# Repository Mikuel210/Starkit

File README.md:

Starkit is a thrust vector controlled electric model rocket designed for propulsive landings

## Project description

I'm building an electric model rocket capable of taking off vertically, hovering and landing propulsively by using thrust vector control (TVC).

- **Propulsion**: I'm using two counter rotating brushless motors and 7" propellers. Each motor is powered by its own 6S LiPo battery and 60A ESC.
- **Avionics**: The main flight computer is an ESP32. I'm using an MPU9250 for orientation and a TF-Luna LiDAR for measuring altitude.
- **Control**: I'm using four TVC vanes driven by four Corona DS918MG servos.
- **Software**: I'm using PID algorithms for controlling orientation and altitude.
- **Structure**: The structure is built from 5mm carbon fiber rods. The rods are locked into 3D printed structural parts that hold mounts to attach the components as well.
- **Landing gear**: I'm using deployable landing gear, actuated by four SG90 servos. Each landing leg is made of a two part design that locks the leg in place once deployed.

## Goal of the project

**To learn and have fun by building an electric model rocket capable of lifting off, hovering and landing propulsively**

I want to build a fully reusable vehicle capable of landing propulsively through thrust vector control. If the rocket is capable of performing a 1 meter hop and hover for 30 seconds, I will consider it a success.

### Why I'm building this project

- To learn about avionics and PCB design
- To learn about software, communication and control systems
- To learn about rocket design
- To learn about CAD and project planning

## PCB

## Wiring diagram

## BOM

| Item                      | Amount | Amount owned | Amount needed | Unit price (€) | Total price (€)    | Link                                                                                                                                                                                                                                                                                                                                                                                                                                                                                                                                                                                                                                                                                                                                                 | Configuration           |
| ------------------------- | ------ | ------------ | ------------- | -------------- | ------------------ | ---------------------------------------------------------------------------------------------------------------------------------------------------------------------------------------------------------------------------------------------------------------------------------------------------------------------------------------------------------------------------------------------------------------------------------------------------------------------------------------------------------------------------------------------------------------------------------------------------------------------------------------------------------------------------------------------------------------------------------------------------- | ----------------------- |
| Batteries                 | 2      |              | 2             | 21,50 €        | 42,99 €            | https://www.amazon.es/HRB-reemplazo-bater%C3%ADa-helic%C3%B3pteros-multicopter/dp/B08TBQKL5B?__mk_es_ES=%C3%85M%C3%85%C5%BD%C3%95%C3%91&crid=2U28Y8KBC8R6M&dib=eyJ2IjoiMSJ9.LXgd79wYVsAlYN8cnheOxOF4z8WHjVPr62UBUdfznEQJUaDWFurwLly_Y13YaV3RCzLjk-IxK2Fx9W1uenqtNgzYBgRNuDVj7gfl4NINt41JqlagWhER4W6rHc6h9dRlsdaZ5Ce64atc4zXVoRv13AauXNFDNE45YwVqKeBIqNpf9GEJRRZUNdxUH4Pl90CMlF84Z880-oE7fsl0TjBh_6v0BYAjIXQ1fz_dwNbMJv1PuqQj3wlPIk55cYDsAPc5loPb8o5-Sp9KXF6ivD4jsehSx9MazX_DaFdfXWazJdw.h3kvJfKKLavn0LHZoaGCOh_W49E9_VzB4I3oYA7u7xY&dib_tag=se&keywords=6s+lipo&qid=1749288373&sprefix=6s+lip%2Caps%2C153&sr=8-46                                                                                                                                    |                         |
| ESCs                      | 2      |              | 2             | 18,59 €        | 37,18 €            | https://es.aliexpress.com/item/1005007477046035.html?spm=a2g0o.productlist.main.3.386577c09KkIA9&algo_pvid=33246dc7-7638-46ad-b82a-8027f90a3399&algo_exp_id=33246dc7-7638-46ad-b82a-8027f90a3399-2&pdp_ext_f=%7B%22order%22%3A%221041%22%2C%22eval%22%3A%221%22%2C%22orig_sl_item_id%22%3A%221005007477046035%22%2C%22orig_item_id%22%3A%221005006909796101%22%7D&pdp_npi=4%40dis%21EUR%2125.40%2112.19%21%21%21203.69%2197.76%21%40211b80e117493716014395182e0aa8%2112000040910350509%21sea%21ES%210%21ABX&curPageLogUid=Syvg8hf9kOqB&utparam-url=scene%3Asearch%7Cquery_from%3A#nav-specification                                                                                                                                                  | Flier 60A V2            |
| Motors                    | 2      |              | 2             | 19,59 €        | 39,18 €            | https://es.aliexpress.com/item/1005005975992937.html?spm=a2g0o.productlist.main.8.504bn3sun3supR&algo_pvid=37cce2c5-c8eb-4d84-a651-7cc254a33470&algo_exp_id=37cce2c5-c8eb-4d84-a651-7cc254a33470-7&pdp_ext_f=%7B%22order%22%3A%227%22%2C%22eval%22%3A%221%22%7D&pdp_npi=4%40dis%21EUR%2122.93%2119.49%21%21%2125.86%2121.98%21%40211b816617499737898785401ed436%2112000035134152652%21sea%21ES%210%21ABX&curPageLogUid=8ZItec0QIfi4&utparam-url=scene%3Asearch%7Cquery_from%3A                                                                                                                                                                                                                                                                       | 1PCS KV1300             |
| Propellers                | 2      |              | 2             | 2,50 €         | 5,00 €             | https://immersion974.com/products/2-paires-dalprop-racerstar-cyclone-t7056c-7056-7x5-6x3-longue-portee-fpv-courses-helice?variant=37636740907168                                                                                                                                                                                                                                                                                                                                                                                                                                                                                                                                                                                                     |                         |
| Leg servos                | 4      | 2            | 2             | 1,07 €         | 2,13 €             | https://es.aliexpress.com/item/1005006572297006.html?spm=a2g0o.productlist.main.2.6d327beakrE4nq&algo_pvid=2c0991c4-8ac1-4d60-aff7-97e9de4a23dd&algo_exp_id=2c0991c4-8ac1-4d60-aff7-97e9de4a23dd-1&pdp_ext_f=%7B%22order%22%3A%224689%22%2C%22eval%22%3A%221%22%7D&pdp_npi=4%40dis%21EUR%212.71%212.21%21%21%213.03%212.47%21%402103919917492886741265488ec7a9%2112000037705759120%21sea%21ES%210%21ABX&curPageLogUid=Mx4vlddFCr1O&utparam-url=scene%3Asearch%7Cquery_from%3A                                                                                                                                                                                                                                                                        | 2Pcs 180 Degree         |
| TVC servos                | 4      |              | 4             | 9,64 €         | 38,55 €            | https://es.aliexpress.com/item/1005002272302617.html                                                                                                                                                                                                                                                                                                                                                                                                                                                                                                                                                                                                                                                                                                 | With 25mm arm x4        |
| Structure rods            | 20     |              | 20            | 2,03 €         | 40,50 €            | https://es.aliexpress.com/item/1005004263451845.html?spm=a2g0o.productlist.main.1.761ceYmheYmhd6&algo_pvid=e5415fe3-4327-4676-a66d-658a9bb2db3f&algo_exp_id=e5415fe3-4327-4676-a66d-658a9bb2db3f-0&pdp_ext_f=%7B%22order%22%3A%221623%22%2C%22eval%22%3A%221%22%7D&pdp_npi=4%40dis%21EUR%213.57%213.07%21%21%2128.65%2124.64%21%40211b431017492896503426651e8be3%2112000038328676176%21sea%21ES%210%21ABX&curPageLogUid=qhARfsXnKG4c&utparam-url=scene%3Asearch%7Cquery_from%3A                                                                                                                                                                                                                                                                      | 5Pcs 5.0x500mm          |
| Leg struts                | 8      |              | 8             | 0,77 €         | 6,19 €             | https://es.aliexpress.com/item/1005004263451845.html?spm=a2g0o.productlist.main.1.761ceYmheYmhd6&algo_pvid=e5415fe3-4327-4676-a66d-658a9bb2db3f&algo_exp_id=e5415fe3-4327-4676-a66d-658a9bb2db3f-0&pdp_ext_f=%7B%22order%22%3A%221623%22%2C%22eval%22%3A%221%22%7D&pdp_npi=4%40dis%21EUR%213.57%213.07%21%21%2128.65%2124.64%21%40211b431017492896503426651e8be3%2112000038328676176%21sea%21ES%210%21ABX&curPageLogUid=qhARfsXnKG4c&utparam-url=scene%3Asearch%7Cquery_from%3A                                                                                                                                                                                                                                                                      | 10Pcs 3.0x500mm         |
| Leg springs               | 4      |              | 4             | 0,43 €         | 1,73 €             | https://es.aliexpress.com/item/4000250320601.html?spm=a2g0o.productlist.main.1.5f69144ec1rYDm&algo_pvid=0e2fdce4-f2c5-40f6-83f7-67ac9305241b&algo_exp_id=0e2fdce4-f2c5-40f6-83f7-67ac9305241b-0&pdp_ext_f=%7B%22order%22%3A%221365%22%2C%22eval%22%3A%221%22%7D&pdp_npi=4%40dis%21EUR%211.34%210.99%21%21%211.50%211.11%21%40211b617b17492888951613089eab25%2112000026870638881%21sea%21ES%210%21ABX&curPageLogUid=aOtvWOKUPPKC&utparam-url=scene%3Asearch%7Cquery_from%3A                                                                                                                                                                                                                                                                           | 30mm 0.3 x 4            |
| PETG filament             | 1      | 1            | 0             | 16,99 €        | 0,00 €             | https://eu.store.bambulab.com/es/products/petg-translucent?id=49192018149724                                                                                                                                                                                                                                                                                                                                                                                                                                                                                                                                                                                                                                                                         |                         |
| Velcro                    | 10     |              | 10            | 0,15 €         | 1,53 €             | https://es.aliexpress.com/item/1005008063390791.html?spm=a2g0o.productlist.main.7.7935CBDhCBDhJD&algo_pvid=82ab8097-120f-49c0-bfd2-9221ed149b58&algo_exp_id=82ab8097-120f-49c0-bfd2-9221ed149b58-6&pdp_ext_f=%7B%22order%22%3A%222119%22%2C%22eval%22%3A%221%22%7D&pdp_npi=4%40dis%21EUR%211.15%210.99%21%21%219.21%217.95%21%4021039a5b17492912680996755eeb12%2112000043504951494%21sea%21ES%210%21ABX&curPageLogUid=XN77MbkCJ60X&utparam-url=scene%3Asearch%7Cquery_from%3A                                                                                                                                                                                                                                                                        | Rectangle 16x70mm 10pcs |
| Bullet connectors         | 6      |              | 6             | 0,28 €         | 1,66 €             | https://es.aliexpress.com/item/1005006400659486.html?spm=a2g0o.productlist.main.1.37683ccbXgkhPr&algo_pvid=22aa2fc1-add9-4555-bb5d-8170122417b8&algo_exp_id=22aa2fc1-add9-4555-bb5d-8170122417b8-0&pdp_ext_f=%7B%22order%22%3A%223980%22%2C%22eval%22%3A%221%22%7D&pdp_npi=4%40dis%21EUR%211.31%210.99%21%21%211.46%211.10%21%402103867617492898094714028e0921%2112000037032813999%21sea%21ES%210%21ABX&curPageLogUid=pehdywiyloSB&utparam-url=scene%3Asearch%7Cquery_from%3A                                                                                                                                                                                                                                                                        | 6Pair 4.0mm             |
| Cable for motor extension | 1      |              | 1             | 5,59 €         | 5,59 €             | https://es.aliexpress.com/item/1005006566120439.html?spm=a2g0o.productlist.main.1.57f039b470LHsH&algo_pvid=eb01c303-fb0d-48fe-b015-28dc3583114b&algo_exp_id=eb01c303-fb0d-48fe-b015-28dc3583114b-0&pdp_ext_f=%7B%22order%22%3A%224259%22%2C%22eval%22%3A%221%22%7D&pdp_npi=4%40dis%21EUR%216.56%215.40%21%21%2152.57%2143.28%21%40211b816617492903787692996e86a8%2112000037691464138%21sea%21ES%210%21ABX&curPageLogUid=ippPKrVhFn3g&utparam-url=scene%3Asearch%7Cquery_from%3A                                                                                                                                                                                                                                                                      | 3m 12 AWG               |
| Heat shrunk tubing        | 1      |              | 1             | 4,46 €         | 4,46 €             | https://es.aliexpress.com/item/1005005188307524.html?spm=a2g0o.tesla.0.0.4dcej0Zsj0ZsUd&pdp_npi=4%40dis%21EUR%212%2C10€%210%2C99€%21%21%21%21%21%40211b612817500001384372689ec846%2112000032032038883%21btf%21%21%21&afTraceInfo=1005005188307524__pc__c_ppc_item_bridge_pc_main__IQwes0f__1750000138532&gatewayAdapt=glo2esp                                                                                                                                                                                                                                                                                                                                                                                                                        | 580pcs in box           |
| Cable for components      | 1      |              | 1             | 2,44 €         | 2,44 €             | https://es.aliexpress.com/item/1005006566120439.html?spm=a2g0o.productlist.main.2.11a87387Kycknd&algo_pvid=198a24ce-2649-422a-be70-759f7e4ad08c&algo_exp_id=198a24ce-2649-422a-be70-759f7e4ad08c-1&pdp_ext_f=%7B%22order%22%3A%224277%22%2C%22eval%22%3A%221%22%7D&pdp_npi=4%40dis%21EUR%216.49%215.34%21%21%2152.57%2143.24%21%40210384cc17501889223512784eabb6%2112000037691464138%21sea%21ES%210%21ABX&curPageLogUid=Az62DYRaIplh&utparam-url=scene%3Asearch%7Cquery_from%3A                                                                                                                                                                                                                                                                      | Black 5M 20AWG          |
| Charger                   | 1      |              | 1             | 19,67 €        | 19,67 €            | https://es.aliexpress.com/item/1005007326920235.html?spm=a2g0o.productlist.main.25.1ee4130b71LMaE&utparam-url=scene%3Asearch%7Cquery_from%3Apc_back_same_best&algo_pvid=96a50608-e680-4398-9ac8-59a08becccd5&algo_exp_id=96a50608-e680-4398-9ac8-59a08becccd5&pdp_ext_f=%7B%22order%22%3A%224048%22%7D&pdp_npi=4%40dis%21EUR%2156.71%2117.36%21%21%21454.74%21139.15%21%40211b628117492908826713158e85fb%2112000040281503044%21sea%21ES%210%21ABX                                                                                                                                                                                                                                                                                                    |                         |
| LiPo bag                  | 2      |              | 2             | 5,56 €         | 11,12 €            | https://www.amazon.es/KUBDPQOR-bater%C3%ADa-Ign%C3%ADfuga-Explosiones-Proteger/dp/B0D6WDVMMQ?dib=eyJ2IjoiMSJ9.EBP3VYs7h0d46i2jEdIxCKP0RCziNsbeAdRnjLeE8Segq2aCxgiG8TaUSG9pjhEP5kb4TCmJDvvTbySqxWheuOfQSJpC3GV0VFwi3erFFE_vtUzrdDW6SQzrTM4v1oX_-QL77Y4_ZPMVrz8BhAXiTVmv6VJYg3sTffhQAcX2qMmE-DzR8BOlpTaodYAHj2pwl0eXWOGXwQWWrb9GUDiV4g_7BaYk1vnk4mZcEWNol4aLK8bs5B2g2urb97TYCW6RdLv3nLkAx9yHx4zj7G-5H0YhJ4oDjEtXmhuVA_VQWWs.4HBTMUuzYBEyHpB2geBzHTSd5y7LK7zdPYDjDSmmhfM&dib_tag=se&keywords=lipo+safe&qid=1749291023&sr=8-12                                                                                                                                                                                                                           |                         |
| PCB                       | 1      |              | 1             | 0,00 €         | 0,00 €             | https://jlcpcb.com/es/                                                                                                                                                                                                                                                                                                                                                                                                                                                                                                                                                                                                                                                                                                                               |                         |
| LiDAR                     | 1      |              | 1             | 16,93 €        | 16,93 €            | https://es.aliexpress.com/item/1005007773724655.html?spm=a2g0o.detail.pcDetailTopMoreOtherSeller.1.d03cnvSMnvSM4O&gps-id=pcDetailTopMoreOtherSeller&scm=1007.40196.439370.0&scm_id=1007.40196.439370.0&scm-url=1007.40196.439370.0&pvid=257a845b-bd4b-41b9-8eb4-32116a834614&_t=gps-id:pcDetailTopMoreOtherSeller,scm-url:1007.40196.439370.0,pvid:257a845b-bd4b-41b9-8eb4-32116a834614,tpp_buckets:668%232846%238112%231997&pdp_ext_f=%7B%22order%22%3A%22236%22%2C%22eval%22%3A%221%22%2C%22sceneId%22%3A%2230050%22%7D&pdp_npi=4%40dis%21EUR%2157.01%2116.91%21%21%21460.14%21136.51%21%40211b680e17505431540684235eaa38%2112000042158078686%21rec%21ES%21%21ABX&utparam-url=scene%3ApcDetailTopMoreOtherSeller%7Cquery_from%3A#nav-specification |                         |
| IMU                       | 1      |              | 1             | 12,29 €        | 12,29 €            | https://www.amazon.es/MPU%E2%80%919250-giroscopio-magn%C3%A9tico-aceleraci%C3%B3n-medici%C3%B3n/dp/B0BJ31W6KR                                                                                                                                                                                                                                                                                                                                                                                                                                                                                                                                                                                                                                        |                         |
| ESP32                     | 1      |              | 1             | 4,99 €         | 4,99 €             | https://es.aliexpress.com/item/1005008256121637.html?spm=a2g0o.productlist.main.1.46f27592KkhDQ6&aem_p4p_detail=202506080321268011175419467780003631533&algo_pvid=4f7e4e87-e7b9-43e2-9669-503fdb80d1ae&algo_exp_id=4f7e4e87-e7b9-43e2-9669-503fdb80d1ae-0&pdp_ext_f=%7B%22order%22%3A%22257%22%2C%22eval%22%3A%221%22%7D&pdp_npi=4%40dis%21EUR%215.46%214.96%21%21%216.10%215.54%21%40211b6c1917493780866902562efb03%2112000044390358746%21sea%21ES%210%21ABX&curPageLogUid=CkoJWcgnXXZE&utparam-url=scene%3Asearch%7Cquery_from%3A&search_p4p_id=202506080321268011175419467780003631533_1#nav-review                                                                                                                                               | 32D-Type-C-1PCS         |
| Buzzer                    | 1      | 1            | 0             | 0,75 €         | 0,00 €             | https://es.aliexpress.com/item/1005007592230799.html?spm=a2g0o.productlist.main.1.356aC484C484k3&algo_pvid=819561e8-b375-4570-83e4-714f464b8131&algo_exp_id=819561e8-b375-4570-83e4-714f464b8131-0&pdp_ext_f=%7B%22order%22%3A%2246%22%2C%22eval%22%3A%221%22%7D&pdp_npi=4%40dis%21EUR%212.33%210.75%21%21%2118.73%215.99%21%40210390c217503419577143060ed746%2112000041421776769%21sea%21ES%210%21ABX&curPageLogUid=WB7zU00jnQbC&utparam-url=scene%3Asearch%7Cquery_from%3A                                                                                                                                                                                                                                                                         |                         |
| LED                       | 1      | 1            | 0             | 0,70 €         | 0,00 €             | https://es.aliexpress.com/item/1005006942561228.html?spm=a2g0o.productlist.main.2.4f4620eaffVXXM&algo_pvid=2d0dae61-9e8a-4390-b421-1c9e1a1cae35&algo_exp_id=2d0dae61-9e8a-4390-b421-1c9e1a1cae35-1&pdp_ext_f=%7B%22order%22%3A%2251%22%2C%22eval%22%3A%221%22%7D&pdp_npi=4%40dis%21EUR%212.68%210.70%21%21%2121.56%215.61%21%40211b80d117503420023265406e6673%2112000038806749170%21sea%21ES%210%21ABX&curPageLogUid=Ud7lEb62zfWF&utparam-url=scene%3Asearch%7Cquery_from%3A                                                                                                                                                                                                                                                                         |                         |
| Resistors                 | 4      | 4            | 0             | 0,19 €         | 0,00 €             | https://es.aliexpress.com/item/1005007345052730.html?spm=a2g0o.productlist.main.2.4daf4384BgtyYb&algo_pvid=6cfb8a2a-37b7-4e76-8c01-f36b3aa0684e&algo_exp_id=6cfb8a2a-37b7-4e76-8c01-f36b3aa0684e-1&pdp_ext_f=%7B%22order%22%3A%224627%22%2C%22eval%22%3A%221%22%2C%22orig_sl_item_id%22%3A%221005007345052730%22%2C%22orig_item_id%22%3A%221005007010335100%22%7D&pdp_npi=4%40dis%21EUR%211.60%210.77%21%21%2112.85%216.17%21%40211b807017503420350251565ec044%2112000040354424593%21sea%21ES%210%21ABX&curPageLogUid=8nPfyjNQNS36&utparam-url=scene%3Asearch%7Cquery_from%3A                                                                                                                                                                        |                         |
| Headers                   | 1      |              | 1             | 2,02 €         | 2,02 €             | https://es.aliexpress.com/item/4000873858801.html?spm=a2g0o.productlist.main.1.438aMcaxMcaxHA&algo_pvid=8948f835-3dba-4bb3-a6ef-0351d63cb6cf&algo_exp_id=8948f835-3dba-4bb3-a6ef-0351d63cb6cf-0&pdp_ext_f=%7B%22order%22%3A%223640%22%2C%22eval%22%3A%221%22%7D&pdp_npi=4%40dis%21EUR%212.03%211.53%21%21%212.27%211.71%21%40211b813b17503404308943254e449c%2110000010058190554%21sea%21ES%210%21ABX&curPageLogUid=zYO2SICB1heb&utparam-url=scene%3Asearch%7Cquery_from%3A#nav-specification                                                                                                                                                                                                                                                         |                         |
| Angled headers            | 1      |              | 1             | 1,24 €         | 1,24 €             | https://es.aliexpress.com/item/1005008210852764.html?spm=a2g0o.detail.pcDetailTopMoreOtherSeller.5.1eaeV432V432MN&gps-id=pcDetailTopMoreOtherSeller&scm=1007.40196.439370.0&scm_id=1007.40196.439370.0&scm-url=1007.40196.439370.0&pvid=2362691a-9cfa-40b6-b383-5963bc6e059a&_t=gps-id:pcDetailTopMoreOtherSeller,scm-url:1007.40196.439370.0,pvid:2362691a-9cfa-40b6-b383-5963bc6e059a,tpp_buckets:668%232846%238110%231995&pdp_ext_f=%7B%22order%22%3A%22162%22%2C%22eval%22%3A%221%22%2C%22sceneId%22%3A%2230050%22%7D&pdp_npi=4%40dis%21EUR%211.24%210.99%21%21%211.39%211.11%21%4021038df617505419994764643e6b41%2112000044248658299%21rec%21ES%21%21ABX&utparam-url=scene%3ApcDetailTopMoreOtherSeller%7Cquery_from%3A                         | 5Pin 5PCS               |
| Screw terminals           | 4      |              | 4             | 0,37 €         | 1,48 €             | https://es.aliexpress.com/item/1005003556955422.html?spm=a2g0o.productlist.main.3.3caf577cKYWN3O&algo_pvid=340ecbec-d2a6-419c-bd93-93956aa32efc&algo_exp_id=340ecbec-d2a6-419c-bd93-93956aa32efc-1&pdp_ext_f=%7B%22order%22%3A%22552%22%2C%22eval%22%3A%221%22%7D&pdp_npi=4%40dis%21EUR%211.59%210.99%21%21%211.78%211.11%21%40210390c217503411498531989ed743%2112000026274837536%21sea%21ES%210%21ABX&curPageLogUid=msIM3PVHPRlV&utparam-url=scene%3Asearch%7Cquery_from%3A                                                                                                                                                                                                                                                                         | 2Pin 5Pcs               |
| Magnetic balancer         | 1      |              | 1             | 10,52 €        | 10,52 €            | https://www.amazon.es/Hobbypower-Multirotor-Propeller-Magn%C3%A9tico-Quadcopter/dp/B00GSKSFM6?__mk_es_ES=%C3%85M%C3%85%C5%BD%C3%95%C3%91&crid=1Y3D0M00HPAML&dib=eyJ2IjoiMSJ9.TuTH0MKorCpoiaKcuztv5uWmJWleMAYXeDQycNbQ4IHivDQ105jsGrrjYZ11Sx7rg6FHVSvKujnNcWT_9lNPbTIiUqPn2WHdsZ_zTbJQcPzBM1D9I71DuqtkUYKXEyrq6ng_BWkLqkpwmIwsPoCh9qeQeEqdkKkKAp9_YUOeBDmXgSaBJmB1Kgr4bQ4joYWMVLeG3Xx2xtgtuxQfYcW465nYuV7QSnTvXNQ15mXIQQFIjNy7ab1Ct7_8X6uE0uhkFchynzrup0nNjkwCBmpCAtYj_57xiFfdTUPbxArW8O8.HO9O6JUpm8p1K876pSry3QmQJbRnl_hQBwxro1-oBcA&dib_tag=se&keywords=propeller+balancer&qid=1750349895&sprefix=propeller+balancer%2Caps%2C152&sr=8-2                                                                                                             |                         |
| TOTAL                     |        |              |               |                | 309,39 € ($359.67) |                                                                                                                                                                                                                                                                                                                                                                                                                                                                                                                                                                                                                                                                                                                                                      |                         |

***

Made with ❤️ for Highway thanks to Hack Club

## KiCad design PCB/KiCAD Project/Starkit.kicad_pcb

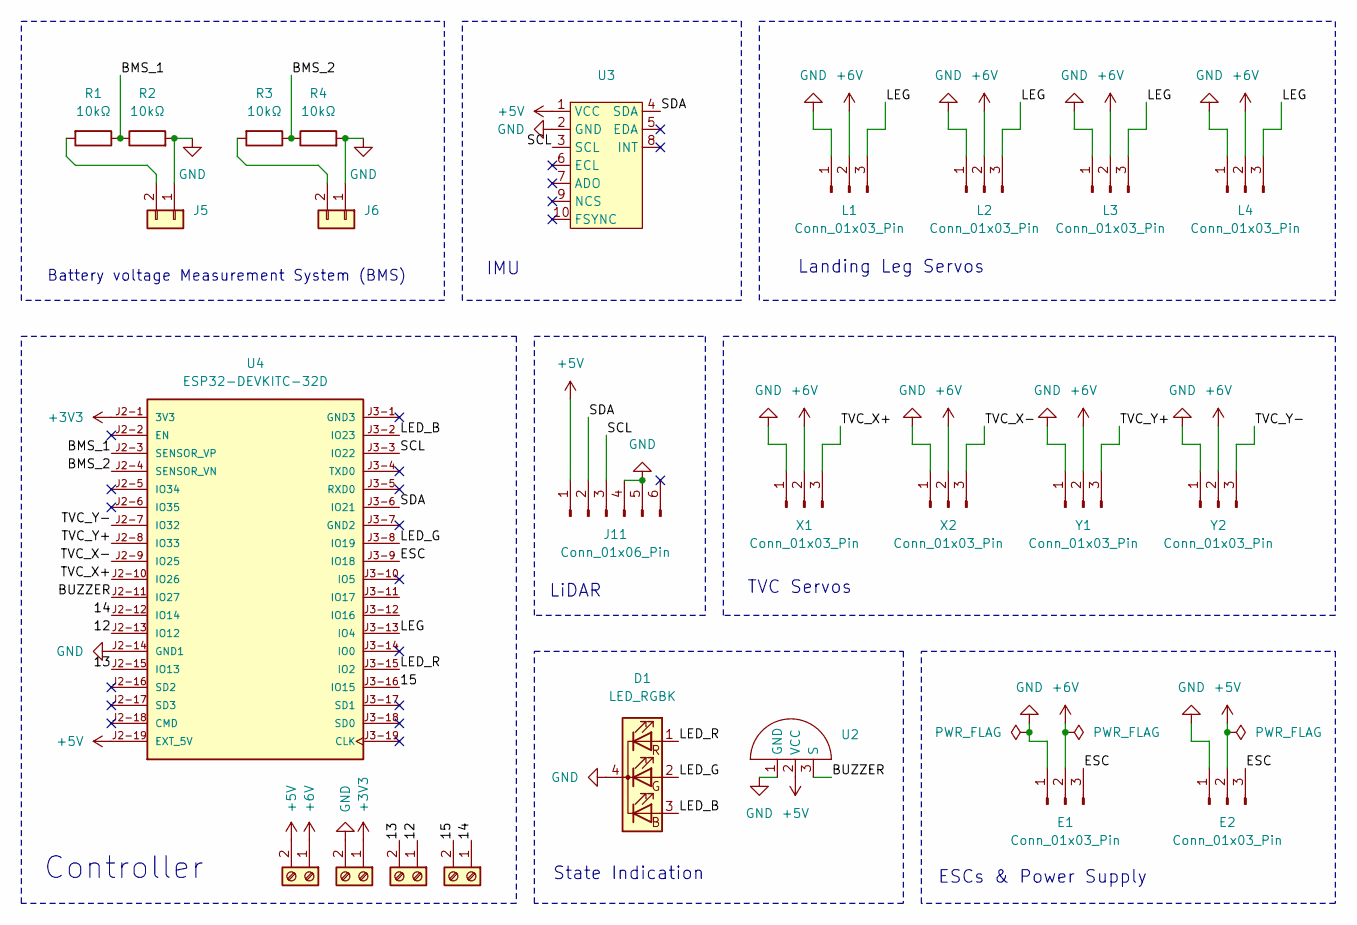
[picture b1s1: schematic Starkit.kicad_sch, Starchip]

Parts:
D1: LED_RGBK; KY-016
E1, E2: Conn_01x03_Pin; PinHeader_1x03_P2.54mm_Vertical
J1, J2, J3, J4: Screw_Terminal_01x02; HANDSON_KF301-2P
J5, J6: Conn_01x02; PinSocket_1x02_P2.54mm_Vertical
J11: Conn_01x06_Pin; PinSocket_1x06_P2.54mm_Vertical
L1, L2, L3, L4: Conn_01x03_Pin; PinHeader_1x03_P2.54mm_Vertical
R1, R2, R3, R4: 10kΩ; R_Axial_DIN0207_L6.3mm_D2.5mm_P7.62mm_Horizontal
U2: KY-012
U3: GY-9250
U4: ESP32-DEVKITC-32D; MODULE_ESP32-DEVKITC-32D; PARTREV V4; DigiKey_Part_Number 1965-1000-ND
X1, X2: Conn_01x03_Pin; PinHeader_1x03_P2.54mm_Vertical
Y1, Y2: Conn_01x03_Pin; PinHeader_1x03_P2.54mm_Vertical

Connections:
+3V3: J2.1, U4.J2-1 (3V3)
+5V: E2.2, J1.2, J11.1, U2.2 (VCC), U3.1 (VCC), U4.J2-19 (EXT_5V)
+6V: E1.2, J1.1, L1.2, L2.2, L3.2, L4.2, X1.2, X2.2, Y1.2, Y2.2
/12: J3.1, U4.J2-13 (IO12)
/13: J3.2, U4.J2-15 (IO13)
/14: J4.1, U4.J2-12 (IO14)
/15: J4.2, U4.J3-16 (IO15)
/BMS_1: R1.1, R2.1, U4.J2-3 (SENSOR_VP)
/BMS_2: R3.1, R4.1, U4.J2-4 (SENSOR_VN)
/BUZZER: U2.3 (S), U4.J2-11 (IO27)
/ESC: E1.3, E2.3, U4.J3-9 (IO18)
/LED_B: D1.3 (BA), U4.J3-2 (IO23)
/LED_G: D1.2 (GA), U4.J3-8 (IO19)
/LED_R: D1.1 (RA), U4.J3-15 (IO2)
/LEG: L1.3, L2.3, L3.3, L4.3, U4.J3-13 (IO4)
/SCL: J11.3, U3.3 (SCL), U4.J3-3 (IO22)
/SDA: J11.2, U3.4 (SDA), U4.J3-6 (IO21)
/TVC_X+: U4.J2-10 (IO26), X1.3
/TVC_X-: U4.J2-9 (IO25), X2.3
/TVC_Y+: U4.J2-8 (IO33), Y1.3
/TVC_Y-: U4.J2-7 (IO32), Y2.3
GND: D1.4 (K), E1.1, E2.1, J2.2, J5.1, J6.1, J11.4, J11.5, L1.1, L2.1, L3.1, L4.1, R2.2, R4.2, U2.1 (GND), U3.2 (GND), U4.J2-14 (GND1), X1.1, X2.1, Y1.1, Y2.1
unnamed: J5.2, R1.2
unnamed: J6.2, R3.2

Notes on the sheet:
IMU
Battery voltage Measurement System (BMS)
Landing Leg Servos
Controller
LiDAR
ESCs & Power Supply
TVC Servos
State Indication

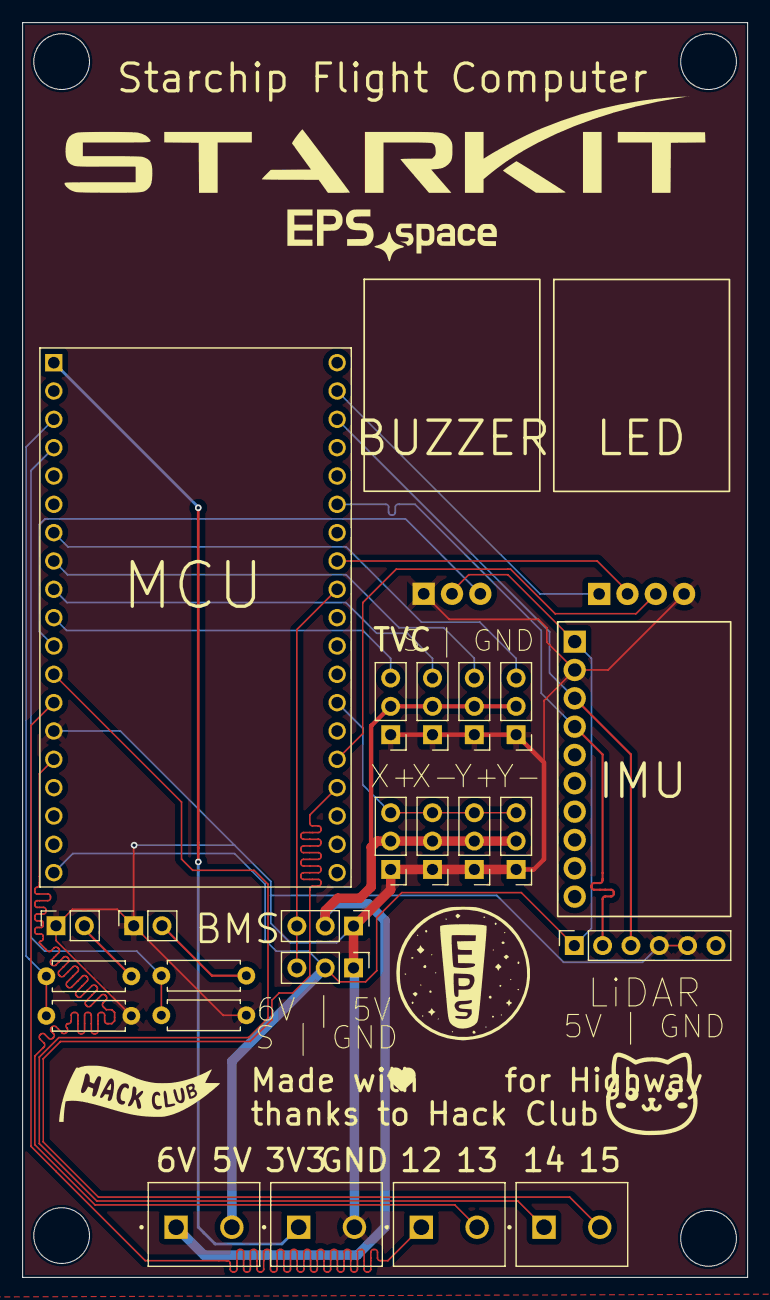
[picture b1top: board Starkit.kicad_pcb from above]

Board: 2 copper layers, 65.0 x 112.5 mm, 25 parts (0 on the bottom side), 24 nets.

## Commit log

2025-05-22 22-05-2025
2025-05-22 asdf
2025-05-24 24-05-2025
2025-05-27 25-05-2025
2025-05-27 27-05-2025
2025-05-29 29-05-2025
2025-05-30 31-05-2025
2025-06-01 01-06-2025
2025-06-03 03-06-2025
2025-06-04 04-06-2025
2025-06-06 06-06-2025
2025-06-08 07-06-2025
2025-06-08 08-06-2025
2025-06-12 12-06-2025
2025-06-13 13-06-2025
2025-06-22 21-06-2025
2025-06-23 23-06-2025
2025-06-25 25-06-2025
2025-06-26 26-06-2025
2025-06-28 28-06-2025
2025-07-09 09-07-2025
2025-10-05 05/10/2025
2025-10-11 11-10-2025
2025-11-06 27-10-2025
2026-01-07 07-01-2026
